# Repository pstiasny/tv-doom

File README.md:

# tv-doom

This repo contains two components:

*  The ESP32-S3-based board sandwich that fits around a battery in
   a 9.5mm antenna plug.
*  A port of Doom for that hardware, including a PAL video and audio
   signal synthesizer.

The detailed description of the build is described in this blog post:

https://raytriangle.com/making-the-worlds-smallest-game-console/

Note that parts of the hardware engineering and almost all
of coding in this project were done in collaboration with Claude.

## Layout

| Path | What |
|---|---|
| `main/` | Game app: engine task, sound subcarrier, clock output, OTA hand-over, crash log, test cards |
| `components/video/` | PAL composite encoder on the RGB-LCD DMA engine, plus the compiled-in RF calibration curve |
| `components/gamepad/` | Xbox controller HID-over-GATT client on NimBLE, and a BLE log console |
| `components/power/`, `components/settings/` | Supply/temperature monitoring and NVS-backed settings |
| `components/doomgeneric/` | The Doom engine, vendored. See its README for provenance and local changes |
| `ota_loader/` | Second ESP-IDF project: WiFi + HTTP updater for the factory slot |
| `tools/` | Host-side scripts: WAD flashing, OTA image server, BLE log console, perf stats |
| `hardware/` | tvplug board, KiCad 10 schematic and layout |

## Building

Toolchain: ESP-IDF `v6.1-dev` (tested at git `fa47e101d53`). The NimBLE
settings in `sdkconfig.defaults` work around behaviour specific to that
revision, so an older or newer IDF may need adjusting. Both projects target
the ESP32-S3R8 with 16 MB flash and octal PSRAM.

```sh
. $IDF_PATH/export.sh
idf.py build                       # game -> build/tv-doom.bin
(cd ota_loader && idf.py build)    # loader -> ota_loader/build/ota-loader.bin
```

Host tools need Python 3 with `pip install -r tools/requirements.txt`, run
inside the exported IDF environment so that `esptool` is on the path.

## Flashing

An IWAD is required and is not included. Put `doom.wad` (or the freely
redistributable shareware `doom1.wad`) in `wads/`. `doom2.wad` does not fit the
13.4 MB WAD partition next to the two OTA slots.

The first flash goes over USB and writes everything at once: bootloader,
partition table, OTA data, loader, game and WAD.

```sh
tools/flash_ota_migration.sh /dev/cu.usbmodemXXX wads/doom.wad
```

After that, updates can go over WiFi. Press the home (big X) button on the controller
to reboot into the loader, join a network with the on-screen keyboard,
and pick an image from the server started with `tools/ota.py` on the build
machine. The loader currently has the server address compiled in at the top of
`ota_loader/main/ota_menu.c`; change it to your own.

A game image that crashes before marking itself healthy rolls back to the
loader, and four crash-class resets in a row do the same, so a bad build can
always be replaced without opening the enclosure.

## Hardware

`hardware/` holds the KiCad 10 project for the tvplug2 board. Proprietary
footprints and 3D models are not included.

The physical layout was designed specifically to fit within a "Goobay 11502"
9.5 TV antenna plug and a 601520 150mAh LiPo battery.

The mixer calibration curve in `components/video/rfcal_default.h`
was measured on a real board with a TinySA and a Pluto+ SDR and might need
to be retuned.

Browse in [KiCanvas](https://kicanvas.org/?repo=https%3A%2F%2Fgithub.com%2Fpstiasny%2Ftv-doom%2Ftree%2Fmain%2Fhardware).

## License

The firmware is licensed under the GNU General Public License, version 2 or
later (see `LICENSE`), which is the license of the Doom engine it links
against. The hardware design in `hardware/` is released under CC BY 4.0 (see
`hardware/LICENSE`).

Third-party code:

- `components/doomgeneric/` is Doom, copyright id Software, via Chocolate Doom,
  doomgeneric and the lilka project's embedded fork. GPL-2.0-or-later.
- `components/gamepad/esp_hid_gap.c` is from the ESP-IDF examples, copyright
  Espressif Systems, Unlicense or CC0-1.0.

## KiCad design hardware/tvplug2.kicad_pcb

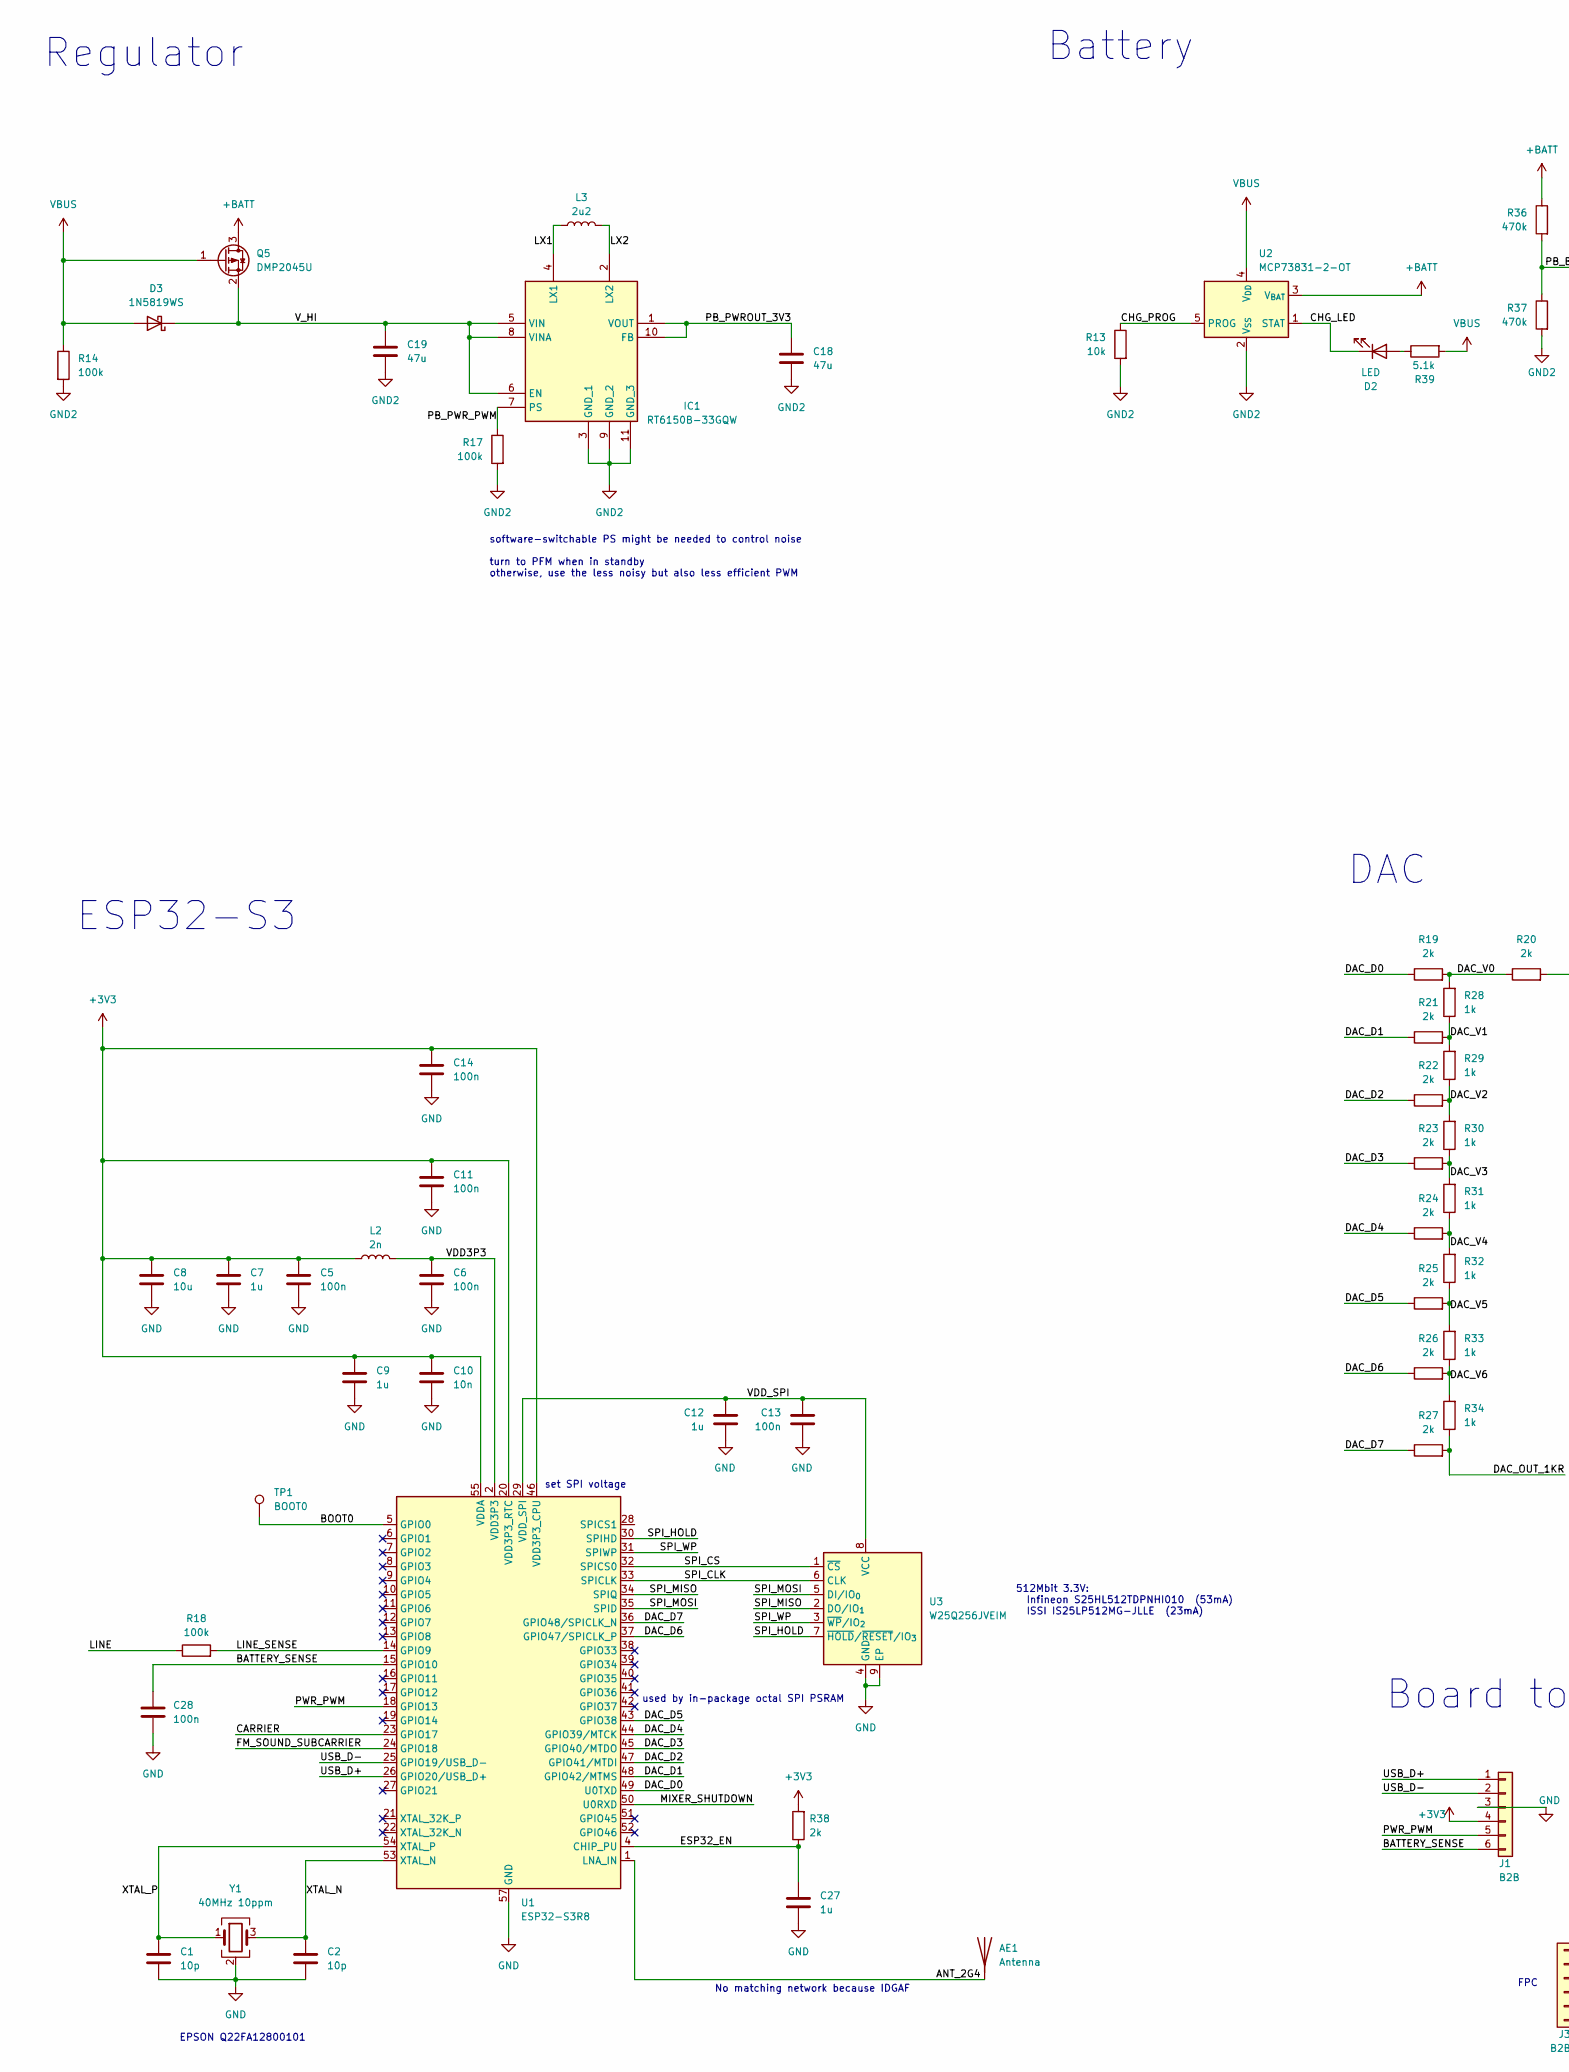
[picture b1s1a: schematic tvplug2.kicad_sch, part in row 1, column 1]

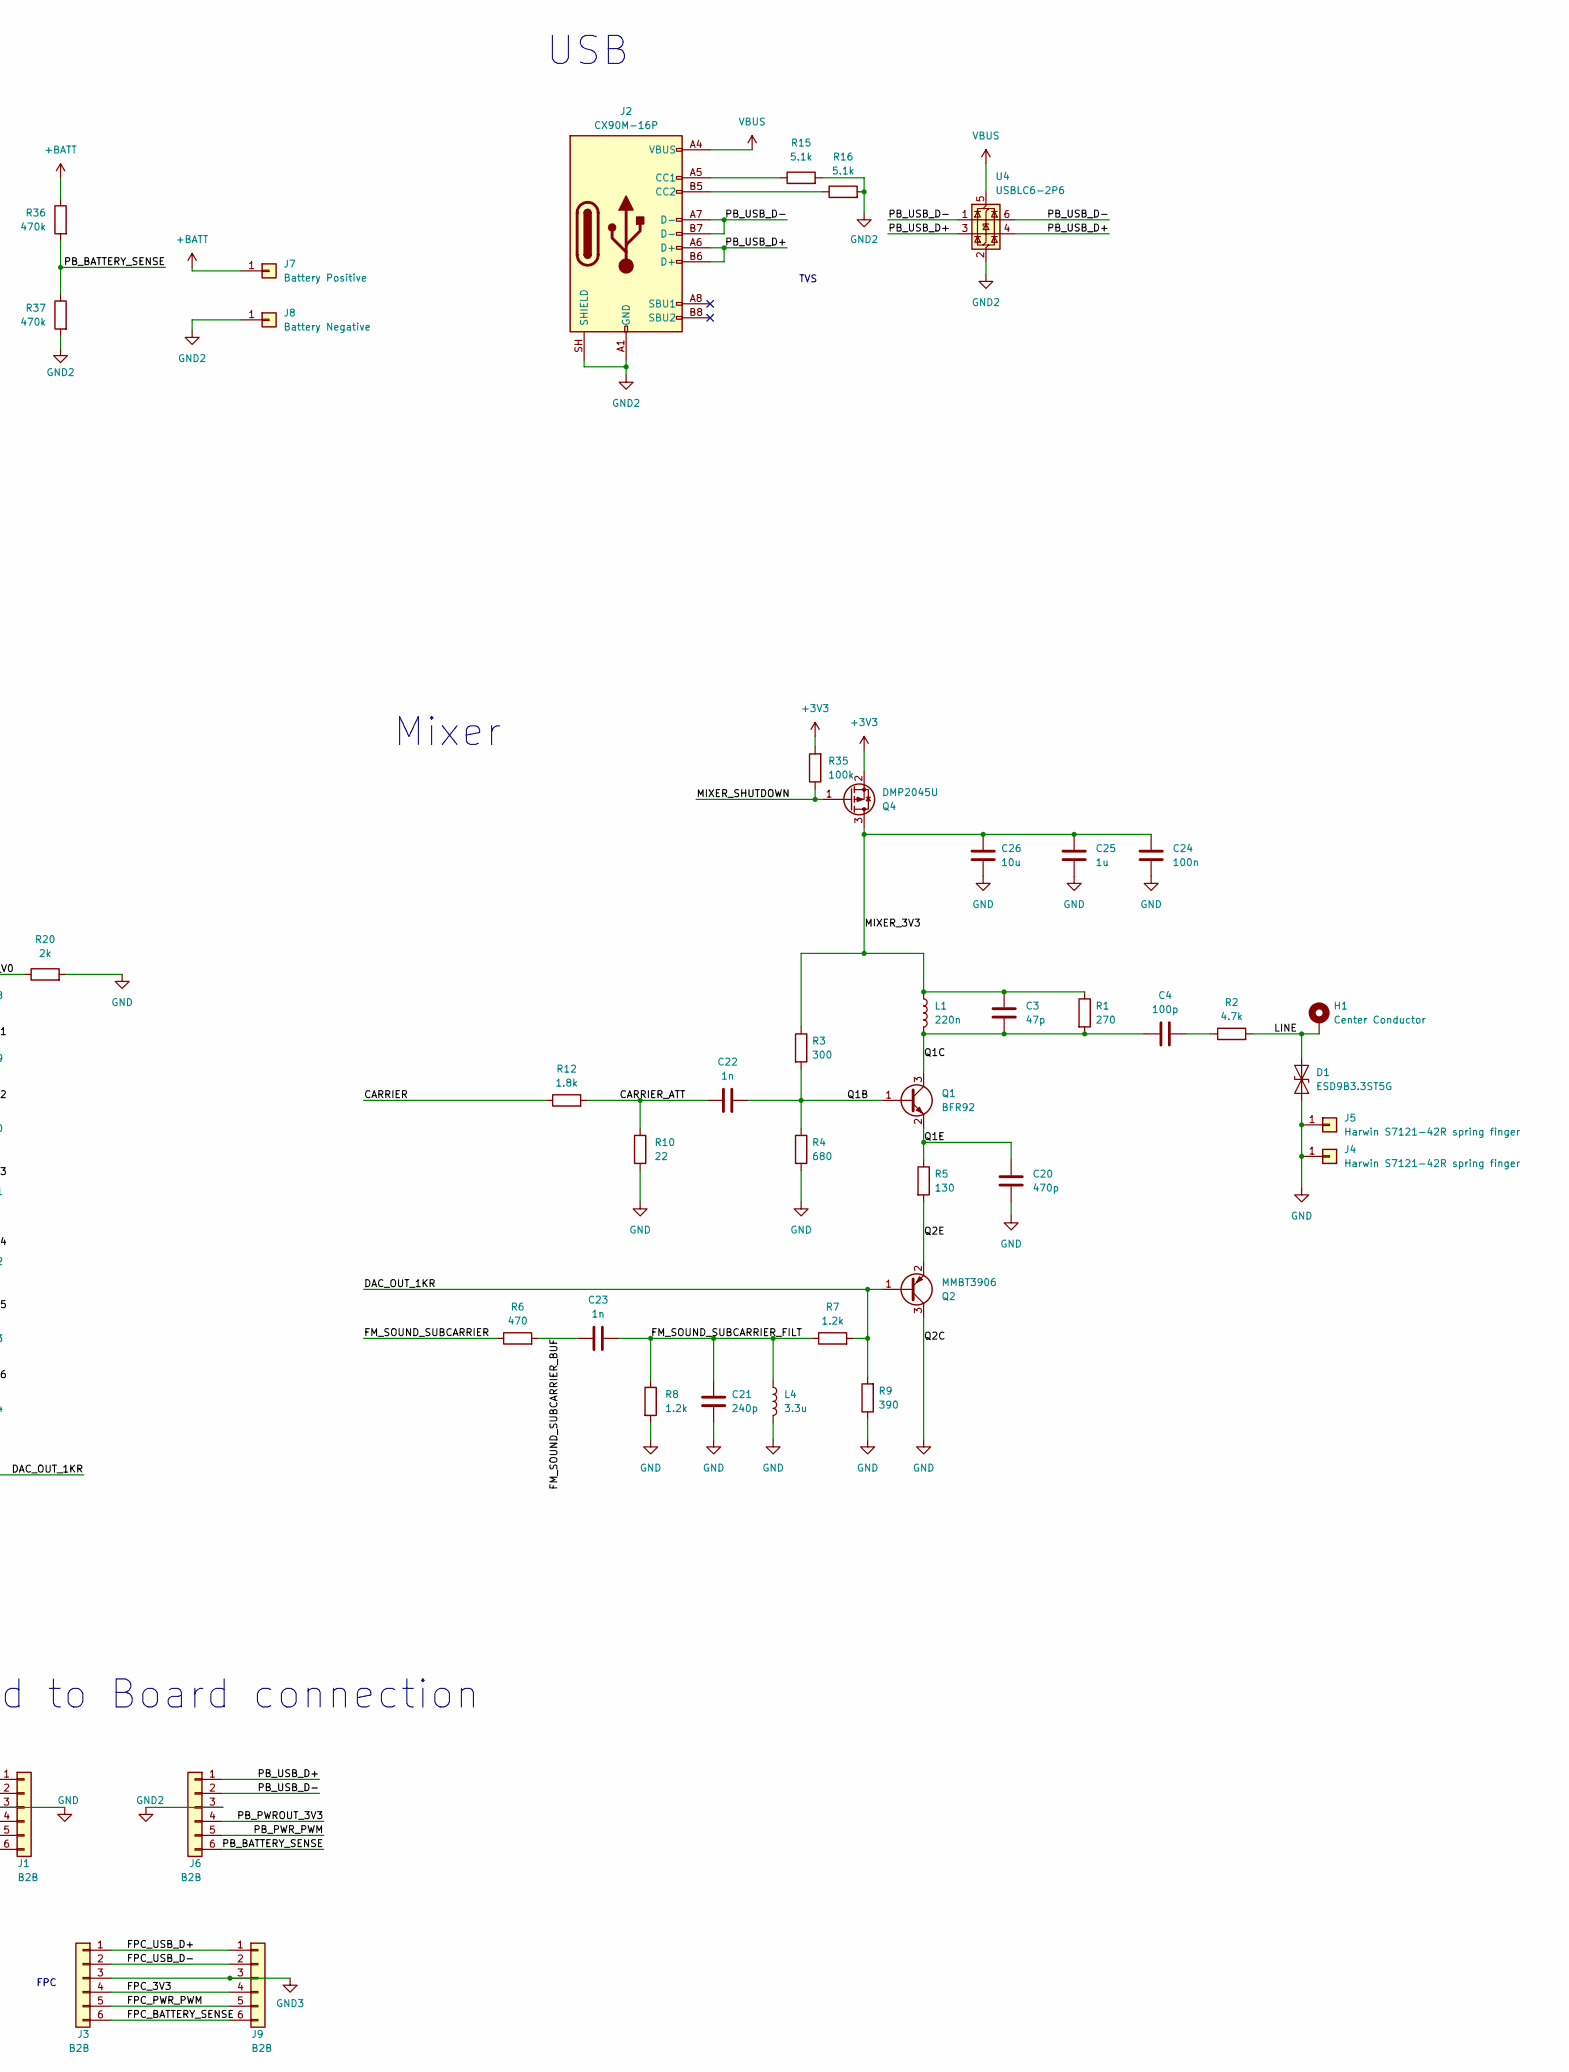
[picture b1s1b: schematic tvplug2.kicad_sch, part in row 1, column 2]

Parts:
AE1: Antenna; TestPoint_Pad_1.0x1.0mm
C1, C2: 10p; C_0402_1005Metric
C3: 47p; C_0402_1005Metric
C4: 100p; C_0402_1005Metric
C5, C6, C11, C13, C14, C24, C28: 100n; C_0402_1005Metric
C7, C9, C12, C25, C27: 1u; C_0402_1005Metric
C8, C26: 10u; C_0402_1005Metric
C10: 10n; C_0402_1005Metric
C18, C19: 47u; C_0805_2012Metric
C20: 470p; C_0402_1005Metric
C21: 240p; C_0402_1005Metric
C22, C23: 1n; C_0402_1005Metric
D1: ESD9B3.3ST5G; D_SOD-923
D2: LED; LED_0603_1608Metric
D3: 1N5819WS; D_SOD-323
H1: Center Conductor; MountingHole_3.2mm_M3_Pad_Via
IC1: RT6150B-33GQW; SON50P250X250X80-11N-D; Mouser Part Number 835-RT6150B-33GQW
J1, J6: B2B; B2B_flex
J2: CX90M-16P; USB_C_Receptacle_Hirose_CX90M-16P_MidMount
J3, J9: B2B; B2B_flex_opposite
J4, J5: Harwin S7121-42R spring finger; S712142R
J7: Battery Positive; SolderWirePad_1x01_SMD_1.5x3mm
J8: Battery Negative; SolderWirePad_1x01_SMD_1.5x3mm
L1: 220n; L_0402_1005Metric
L2: 2n; L_0402_1005Metric
L3: 2u2; SPM3010-3020
L4: 3.3u; L_0402_1005Metric
Q1: BFR92; SOT-323_SC-70
Q2: MMBT3906; SOT-23
Q4, Q5: DMP2045U; SOT-23
R1: 270; R_0402_1005Metric
R2: 4.7k; R_0402_1005Metric
R3: 300; R_0402_1005Metric
R4: 680; R_0402_1005Metric
R5: 130; R_0402_1005Metric
R6: 470; R_0402_1005Metric
R7, R8: 1.2k; R_0402_1005Metric
R9: 390; R_0402_1005Metric
R10: 22; R_0402_1005Metric
R12: 1.8k; R_0402_1005Metric
R13: 10k; R_0402_1005Metric
R14, R17, R18, R35: 100k; R_0402_1005Metric
R15, R16, R39: 5.1k; R_0402_1005Metric
R19, R20, R21, R22, R23, R24, R25, R26, R27, R38: 2k; R_0402_1005Metric
R28, R29, R30, R31, R32, R33, R34: 1k; R_0402_1005Metric
R36, R37: 470k; R_0402_1005Metric
TP1: BOOT0; TestPoint_Pad_D1.0mm
U1: ESP32-S3R8; QFN-56-1EP_7x7mm_P0.4mm_EP4x4mm
U2: MCP73831-2-OT; SOT-23-5
U3: W25Q256JVEIM; WSON-8-1EP_8x6mm_P1.27mm_EP3.4x4.3mm
U4: USBLC6-2P6; SOT-666
Y1: 40MHz 10ppm; Crystal_SMD_2016-4Pin_2.0x1.6mm

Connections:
+3V3: C5.1, C7.1, C8.1, C9.1, C10.1, C11.1, C14.1, J1.4, L2.1, Q4.2 (S), R35.2, R38.2, U1.20 (VDD3P3_RTC), U1.46 (VDD3P3_CPU), U1.55 (VDDA), U1.56 (VDDA)
+BATT: J7.1 (Pin_1_1), Q5.3 (D), R36.1, U2.3 (V_{BAT})
/ANT_2G4: AE1.1 (A_1), U1.1 (LNA_IN)
/BATTERY_SENSE: C28.2, J1.6, U1.15 (GPIO10)
/BOOT0: TP1.1 (1_1), U1.5 (GPIO0)
/CARRIER: R12.1, U1.23 (GPIO17)
/CARRIER_ATT: C22.1, R10.1, R12.2
/CHG_LED: D2.1 (K), U2.1 (STAT)
/CHG_PROG: R13.1, U2.5 (PROG)
/DAC_D0: R19.1, U1.49 (U0TXD)
/DAC_D1: R21.1, U1.48 (GPIO42/MTMS)
/DAC_D2: R22.1, U1.47 (GPIO41/MTDI)
/DAC_D3: R23.1, U1.45 (GPIO40/MTDO)
/DAC_D4: R24.1, U1.44 (GPIO39/MTCK)
/DAC_D5: R25.1, U1.43 (GPIO38)
/DAC_D6: R26.1, U1.37 (GPIO47/SPICLK_P)
/DAC_D7: R27.1, U1.36 (GPIO48/SPICLK_N)
/DAC_OUT_1KR: Q2.1 (B), R7.2, R9.2, R27.2, R34.1
/DAC_V0: R19.2, R20.1, R28.2
/DAC_V1: R21.2, R28.1, R29.2
/DAC_V2: R22.2, R29.1, R30.2
/DAC_V3: R23.2, R30.1, R31.2
/DAC_V4: R24.2, R31.1, R32.2
/DAC_V5: R25.2, R32.1, R33.2
/DAC_V6: R26.2, R33.1, R34.2
/ESP32_EN: C27.1, R38.1, U1.4 (CHIP_PU)
/FM_SOUND_SUBCARRIER: R6.1, U1.24 (GPIO18)
/FM_SOUND_SUBCARRIER_BUF: C23.1, R6.2
/FM_SOUND_SUBCARRIER_FILT: C21.1, C23.2, L4.1, R7.1, R8.1
/FPC_3V3: J3.4, J9.4
/FPC_BATTERY_SENSE: J3.6, J9.6
/FPC_PWR_PWM: J3.5, J9.5
/FPC_USB_D+: J3.1, J9.1
/FPC_USB_D-: J3.2, J9.2
/LINE: D1.2 (A2), H1.1 (1_1), R2.2, R18.1
/LINE_SENSE: R18.2, U1.14 (GPIO9)
/LX1: IC1.4 (LX1), L3.1
/LX2: IC1.2 (LX2), L3.2
/MIXER_3V3: C3.1, C24.1, C25.1, C26.1, L1.1, Q4.3 (D), R1.1, R3.1
/MIXER_SHUTDOWN: Q4.1 (G), R35.1, U1.50 (U0RXD)
/PB_BATTERY_SENSE: J6.6, R36.2, R37.1
/PB_PWROUT_3V3: C18.1, IC1.1 (VOUT), IC1.10 (FB), J6.4
/PB_PWR_PWM: IC1.7 (PS), J6.5, R17.1
/PB_USB_D+: J2.A6 (D+), J2.B6 (D+), J6.1, U4.3 (I/O2), U4.4 (I/O2)
/PB_USB_D-: J2.A7 (D-), J2.B7 (D-), J6.2, U4.1 (I/O1), U4.6 (I/O1)
/PWR_PWM: J1.5, U1.18 (GPIO13)
/Q1B: C22.2, Q1.1 (B), R3.2, R4.1
/Q1C: C3.2, C4.1, L1.2, Q1.3 (C), R1.2
/Q1E: C20.1, Q1.2 (E), R5.1
/Q2E: Q2.2 (E), R5.2
/SPI_CLK: U1.33 (SPICLK), U3.6 (CLK)
/SPI_CS: U1.32 (SPICS0), U3.1 (~CS)
/SPI_HOLD: U1.30 (SPIHD), U3.7 (~HOLD/~RESET/IO_{3})
/SPI_MISO: U1.34 (SPIQ), U3.2 (DO/IO_{1})
/SPI_MOSI: U1.35 (SPID), U3.5 (DI/IO_{0})
/SPI_WP: U1.31 (SPIWP), U3.3 (~WP/IO_{2})
/USB_D+: J1.1, U1.26 (GPIO20/USB_D+)
/USB_D-: J1.2, U1.25 (GPIO19/USB_D-)
/VDD3P3: C6.1, L2.2, U1.2 (VDD3P3), U1.3 (VDD3P3)
/VDD_SPI: C12.1, C13.1, U1.29 (VDD_SPI), U3.8 (VCC)
/V_HI: C19.1, D3.1 (K), IC1.5 (VIN), IC1.6 (EN), IC1.8 (VINA), Q5.2 (S)
/XTAL_N: C2.1, U1.53 (XTAL_N), Y1.3
/XTAL_P: C1.1, U1.54 (XTAL_P), Y1.1
GND: C1.2, C2.2, C5.2, C6.2, C7.2, C8.2, C9.2, C10.2, C11.2, C12.2, C13.2, C14.2, C20.2, C21.2, C24.2, C25.2, C26.2, C27.2, C28.1, D1.1 (A1), J1.3, J4.1 (Pin_1_1), J5.1 (Pin_1_1), L4.2, Q2.3 (C), R4.2, R8.2, R9.1, R10.2, R20.2, U1.57 (GND), U3.4 (GND), U3.9 (EP), Y1.2 (G), Y1.4 (G)
GND2: C18.2, C19.2, IC1.3 (GND_1), IC1.9 (GND_2), IC1.11 (GND_3), J2.A1 (GND), J2.A12 (GND), J2.B1 (GND), J2.B12 (GND), J2.SH (SHIELD), J6.3, J8.1 (Pin_1_1), R13.2, R14.2, R15.2, R16.2, R17.2, R37.2, U2.2 (V_{SS}), U4.2 (GND)
GND3: J3.3, J9.3
unnamed: C4.2, R2.1
unnamed: D2.2 (A), R39.1
unnamed: J2.A5 (CC1), R15.1
unnamed: J2.B5 (CC2), R16.1
VBUS: D3.2 (A), J2.A4 (VBUS), J2.A9 (VBUS), J2.B4 (VBUS), J2.B9 (VBUS), Q5.1 (G), R14.1, R39.2, U2.4 (V_{DD}), U4.5 (VBUS)

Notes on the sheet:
USB
Board to Board connection
EPSON Q22FA12800101
Mixer
DAC
FPC
used by in-package octal SPI PSRAM
ESP32-S3
TVS
Regulator
512Mbit 3.3V: Infineon S25HL512TDPNHI010 (53mA) ISSI IS25LP512MG-JLLE (23mA)
software-switchable PS might be needed to control noise turn to PFM when in standby otherwise, use the less noisy but also less efficient PWM
No matching network because IDGAF
set SPI voltage
Battery

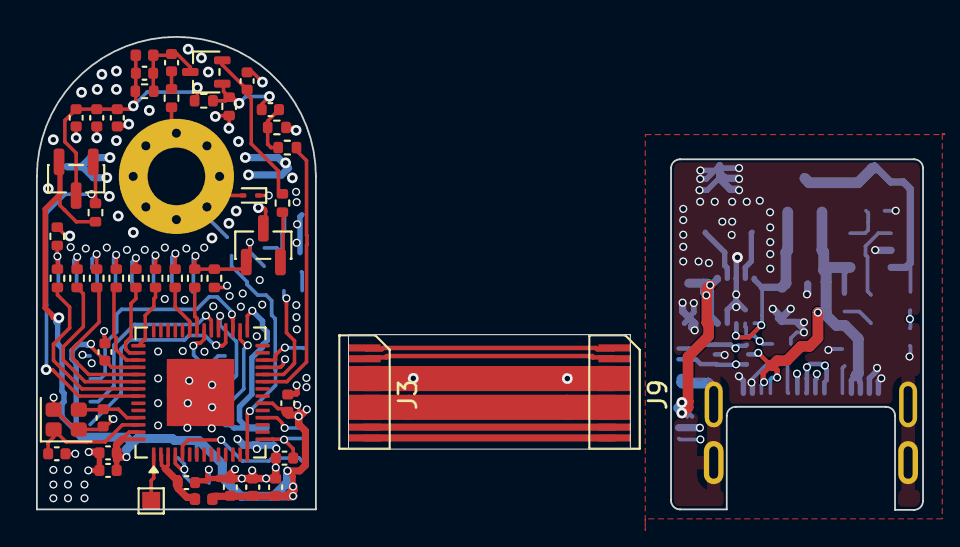
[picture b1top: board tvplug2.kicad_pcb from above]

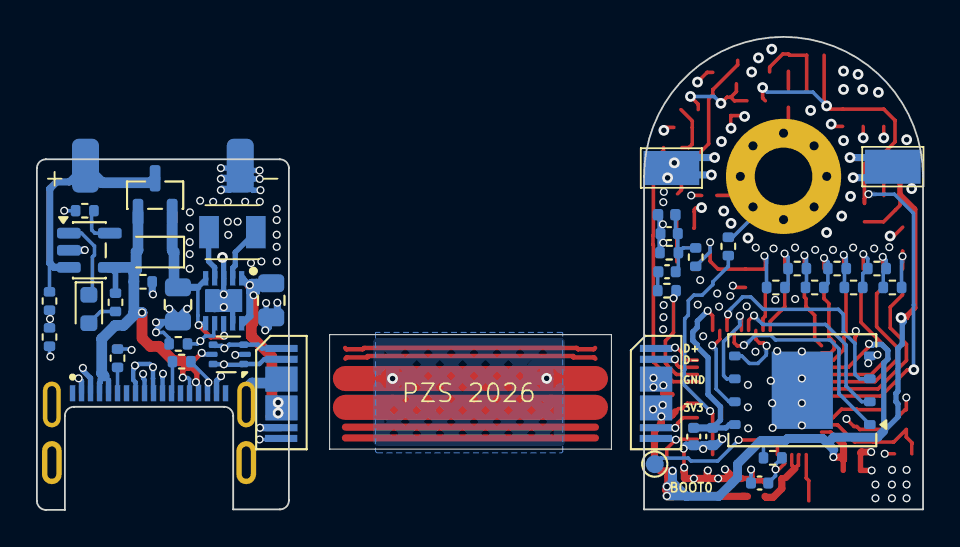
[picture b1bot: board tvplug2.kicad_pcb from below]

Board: 4 copper layers, 49.2 x 26.3 mm, 92 parts (44 on the bottom side), 71 nets.

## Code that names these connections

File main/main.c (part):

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    blelog_set_enabled(settings.ble_debug);   // before gamepad_start() brings BLE up
#endif

    // ADC1 for BATTERY_SENSE (GPIO10) and LINE_SENSE (GPIO9). Early and cheap;
    // nothing else contends for ADC1 on this board.
    power_early_gate();          // may shut down here on a flat pack

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             (unsigned)(heap_caps_get_free_size(MALLOC_CAP_SPIRAM) / 1024),
             (unsigned)(heap_caps_get_free_size(MALLOC_CAP_INTERNAL) / 1024));

    // 48 MHz reference on GPIO17 (I2S0 MCLK, PLL240M/5) -- free-runs in
    // hardware, independent of the LCD_CAM video path and Doom on core 0.
    clkout_start_48mhz();
    clkout_enable_boot_toggle();   // BOOT (GPIO0) toggles the carrier on/off
    mixer_set_enabled(true);       // power Q4's MIXER_3V3 rail (gate low = on)

    // The aerial-load probe gates the carrier, so it can only start once the
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    ESP_LOGI(TAG, "after BT: free internal %u KB",
             (unsigned)(heap_caps_get_free_size(MALLOC_CAP_INTERNAL) / 1024));

    // 5.5 MHz FM sound subcarrier on GPIO18 (I2S1 bitstream) -- summed externally
    // into the video baseband; the 48 MHz mixer upconverts it as intercarrier
    // sound. Takes only a small slice of internal DMA RAM, and is non-fatal.
    if (settings.sound_carrier) {
        sound_start(settings.carrier_mode, settings.carrier_drive);
        DG_SetPcmSink(sound_push_s16);   // route Doom's SFX mixer onto the subcarrier
    } else {
        // No carrier: still own GPIO18 and hold it LOW. Left at its reset
        // default (input, floating) the sound filter's input node floats; the
        // loader parks it low when its carrier is off, so the game must too
        // (carrier-OFF picture-instability suspect, 2026-09-15).
        gpio_config_t off = { .pin_bit_mask = 1ULL << 18, .mode = GPIO_MODE_OUTPUT };
        gpio_config(&off);
        gpio_set_level(18, 0);
        ESP_LOGW(TAG, "sound carrier OFF (settings) -- GPIO18 parked low");
    }

    // Bench: RF test patterns instead of Doom (SETTINGS -> TEST CARD, or the
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
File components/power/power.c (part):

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 * -- only the action gating ignores it. WARNING with this on (plus actions
 * armed) and no TV attached the board deep-sleeps ~POWER_LINE_OPEN_TICKS s
 * after boot and the USB console goes away with it -- the debug connection is
 * LOST until wake (ground LINE_SENSE/aerial pin, or BOOT-hold for download
 * mode). Rolled back 2026-09-13 for exactly that reason; enable both only for
 * a deliberate sleep-current measurement session. */
#define POWER_IGNORE_EXT 0
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#define LINE_SWEEP_DIAG  0
#define LINE_MEAN_DIAG   0

/* Bench switch: leave LINE_SENSE (GPIO9) fully high-Z -- no pull-up,
 * no pull-down, no charge pulses, no ADC clamp reads -- so scope measurements
 * of the aerial/RF node see only the passive network (R18/C4/D1). The monitor
 * keeps logging batt/ext but reports the line as "probe off". Set back to 0
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 * the probe always reports unterminated and ext0 wake would never fire. */
#define LINE_PROBE_OFF   0

#define LINE_GPIO   GPIO_NUM_9
/* PWR_PWM (GPIO13 -> J1.5 -> flex -> J6.5 -> RT6150B PS pin): the buck-boost's
 * mode select. High = forced PWM (constant frequency, lowest output ripple --
 * what the video DAC and RF chain want while running). Low or floating = PFM
 * auto power-save (R17 100k pulls PS to ground on the power board), the right
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 * sleep with no RTC hold needed -- same self-securing pattern as R35 on the
 * mixer P-FET. */
#define PWM_GPIO    GPIO_NUM_13
#define BATT_CHAN   ADC_CHANNEL_9    /* ADC1_CH9 == GPIO10 */
#define LINE_CHAN   ADC_CHANNEL_8    /* ADC1_CH8 == GPIO9  */

/* Hold the line at the rail long enough for it to actually get there. Charging
 * goes through R18 (100k) into whatever hangs off the centre conductor: a bare
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 * by the ADC conversion time rather than the physics. */
#define LINE_HOLD_US     200

/* Clamped-mean threshold, in mV at the pin, with the carrier RUNNING and the
 * internal pull-up holding the bias. Measured on this board:
 *
 *   open line   ~400 mV   swing clips hard on the pad clamp, mean dragged down
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 * pull-down and driven-high all read the same ~0.5 V). */
static void line_set_pull(gpio_pull_mode_t mode)
{
    gpio_set_pull_mode(LINE_GPIO, mode);
    esp_rom_delay_us(LINE_SETTLE_US);
}

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{
    if (s_ready) return;

    gpio_config_t line = {
        .pin_bit_mask = 1ULL << LINE_GPIO,
        .mode         = GPIO_MODE_INPUT,
        /* LINE_PROBE_OFF: park the pin high-Z so the bench sees only the
         * passive network on the aerial node. */
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        .pull_down_en = GPIO_PULLDOWN_DISABLE,
        .intr_type    = GPIO_INTR_DISABLE,
    };
    ESP_ERROR_CHECK(gpio_config(&line));

    /* Regular operation: force the RT6150B into PWM mode for minimum supply
     * ripple under the video/RF load. Runs from power_early_gate(), so the
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#endif

    s_ready = true;
    ESP_LOGI(TAG, "up: line=GPIO9 (digital), batt=GPIO10/ADC1_CH9, "
             "converter=PWM (GPIO13 high), cali %s",
             s_cali_batt ? "curve-fitting" : "NONE (raw scaling)");
}

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 *   1. R18 (100k) works into the pin's own capacitance (~5-10 pF including
 *      package, ESD and track), which is a low-pass at roughly 200-300 kHz.
 *      At the 48 MHz carrier that is ~45 dB of attenuation ON TOP of whatever
 *      is on LINE, so even the open-circuit case arrives at the pin as a few
 *      millivolts.
 *   2. ADC1 tops out around 83 kSPS, so the carrier could not be sampled even
 *      if it survived, and nothing in the path rectifies it -- D1 is a 3.3 V
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
static void line_pad_digital(void)
{
    rtc_gpio_deinit(LINE_GPIO);
    gpio_config_t io = {
        .pin_bit_mask = 1ULL << LINE_GPIO,
        .mode         = GPIO_MODE_INPUT,
        .pull_up_en   = GPIO_PULLUP_DISABLE,
        .pull_down_en = GPIO_PULLDOWN_DISABLE,
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    adc_oneshot_config_channel(s_adc, LINE_CHAN, &ch);
}

/* Charge LINE to the rail through the pin, release it, and read what is left a
 * moment later. This is the "short pulse" probe: it says nothing about DC
 * coupling by itself, but combined with the carrier toggle below it measures
 * the RF amplitude at the node. */
static int line_charge_and_read(int hold_us)
{
    line_pad_digital();
    gpio_set_direction(LINE_GPIO, GPIO_MODE_OUTPUT);
    gpio_set_level(LINE_GPIO, 1);
    esp_rom_delay_us(LINE_CHARGE_US);

    gpio_set_direction(LINE_GPIO, GPIO_MODE_INPUT);   /* release to high-Z */
    line_pad_analog();
    esp_rom_delay_us(hold_us);
    return read_mv(LINE_CHAN, s_cali_line);
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static int line_level_with_pull(gpio_pull_mode_t mode)
{
    line_pad_digital();
    gpio_set_pull_mode(LINE_GPIO, mode);
    esp_rom_delay_us(LINE_SETTLE_US);
    return gpio_get_level(LINE_GPIO);
}

void power_line_probe(power_line_t *out)
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
    /* The whole reason the DC probe is worth doing: the "terminated" condition
     * is a static logic level, so the RTC can wait on it directly. No ULP
     * program and no periodic timer wake are needed -- ext0 sits on GPIO9 with
     * the pull-up held through sleep and wakes the chip the instant a set is
     * plugged in. That is both lower power than polling and instant, rather
     * than up to a poll interval late. */
    rtc_gpio_init(LINE_GPIO);
    rtc_gpio_set_direction(LINE_GPIO, RTC_GPIO_MODE_INPUT_ONLY);
    rtc_gpio_pulldown_dis(LINE_GPIO);
    rtc_gpio_pullup_en(LINE_GPIO);

    /* ext0 needs the RTC peripheral domain left powered, otherwise the pull-up
     * dies with it and the pin floats. */
    esp_sleep_pd_config(ESP_PD_DOMAIN_RTC_PERIPH, ESP_PD_OPTION_ON);
    ESP_ERROR_CHECK(esp_sleep_enable_ext0_wakeup(LINE_GPIO, 0));  /* wake on LOW */

    esp_deep_sleep_start();
}
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
    /* Wake on the aerial too: if the user plugs into a TV we want to come up
     * and at least say why we are not playing, rather than look dead. */
    rtc_gpio_init(LINE_GPIO);
    rtc_gpio_set_direction(LINE_GPIO, RTC_GPIO_MODE_INPUT_ONLY);
    rtc_gpio_pulldown_dis(LINE_GPIO);
    rtc_gpio_pullup_en(LINE_GPIO);
    esp_sleep_pd_config(ESP_PD_DOMAIN_RTC_PERIPH, ESP_PD_OPTION_ON);
    esp_sleep_enable_ext0_wakeup(LINE_GPIO, 0);
    esp_sleep_enable_timer_wakeup(POWER_FLAT_RECHECK_US);

    esp_deep_sleep_start();
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    s_slept_on_line = 0;
    power_wake_n++;                 /* breadcrumb: entered the wake path */

    /* The sleep path put GPIO9 under RTC control (rtc_gpio_init + held
     * pull-up for ext0). That mux SURVIVES the wake: left in place, every
     * later probe reads the held bias (~3.0 V) instead of the line -- a
     * permanent false-TERMINATED (observed 2026-09-15: wake rechecks read
     * ~3000 mV on an open bench line). Return the pad to the digital/analog
     * matrix before any probing. */
    rtc_gpio_deinit(LINE_GPIO);
    rtc_gpio_pullup_dis(LINE_GPIO);
    rtc_gpio_pulldown_dis(LINE_GPIO);

    /* ext0 means the LINE pin itself was pulled low -- an unambiguous
     * external event (a terminated line once R18 is 10k, or a deliberate
     * bench rescue pull). Trust it and boot fully; the monitor's hysteresis
     * re-verifies within seconds and re-sleeps if it was a glitch. Running
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    s_batt_low_ticks = 0;
}

/* Bias the pin to a rail and read the resulting MEAN, with the carrier gated
 * off and on.
 *
 * This is the measurement that matters, and it is not a peak-detector effect:
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    if (s_carrier_gate) s_carrier_gate(carrier_on);

    line_pad_analog();                       /* pad -> analog, pulls cleared */
    rtc_gpio_pullup_dis(LINE_GPIO);
    rtc_gpio_pulldown_dis(LINE_GPIO);
    if (pullup) rtc_gpio_pullup_en(LINE_GPIO);
    else        rtc_gpio_pulldown_en(LINE_GPIO);

    esp_rom_delay_us(5000);                  /* settle: 145k into the node's C */
    return read_mv_avg(LINE_CHAN, s_cali_line);
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
/* Median of N clamped-mean samples, spread across several video fields.
 *
 * The carrier is AM-modulated by the picture, so the clamped mean at the pin
 * carries the whole video envelope -- strong structure at the 15.625 kHz line
 * rate and the 50 Hz field rate, all of it well inside the ~227 kHz corner R18
 * forms with the pin capacitance. (The 48 MHz carrier itself is NOT the
 * problem: the ~31k source impedance at the pin working into the ADC's
 * sample-and-hold capacitor rolls it off long before the sampler sees it.)
 *
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     * priority above the game, which took ~14 fps off Doom for no benefit. */
    if (s_carrier_gate) s_carrier_gate(true);
    line_pad_analog();
    rtc_gpio_pulldown_dis(LINE_GPIO);
    rtc_gpio_pullup_en(LINE_GPIO);
    esp_rom_delay_us(5000);

    for (int i = 0; i < LINE_SAMPLES; i++) {
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        if (s_report_cb) s_report_cb(conn ? batt : -1, ext, l.terminated);

#if LINE_PROBE_OFF
        ESP_LOGI(TAG, "batt %d mV%s | line PROBE OFF (GPIO9 high-Z, bench) | ext %s (host %s)",
                 batt, conn ? "" : " (SENSE DISCONNECTED)",
                 ext ? "YES" : "no", host ? "yes" : "no");
#else
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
